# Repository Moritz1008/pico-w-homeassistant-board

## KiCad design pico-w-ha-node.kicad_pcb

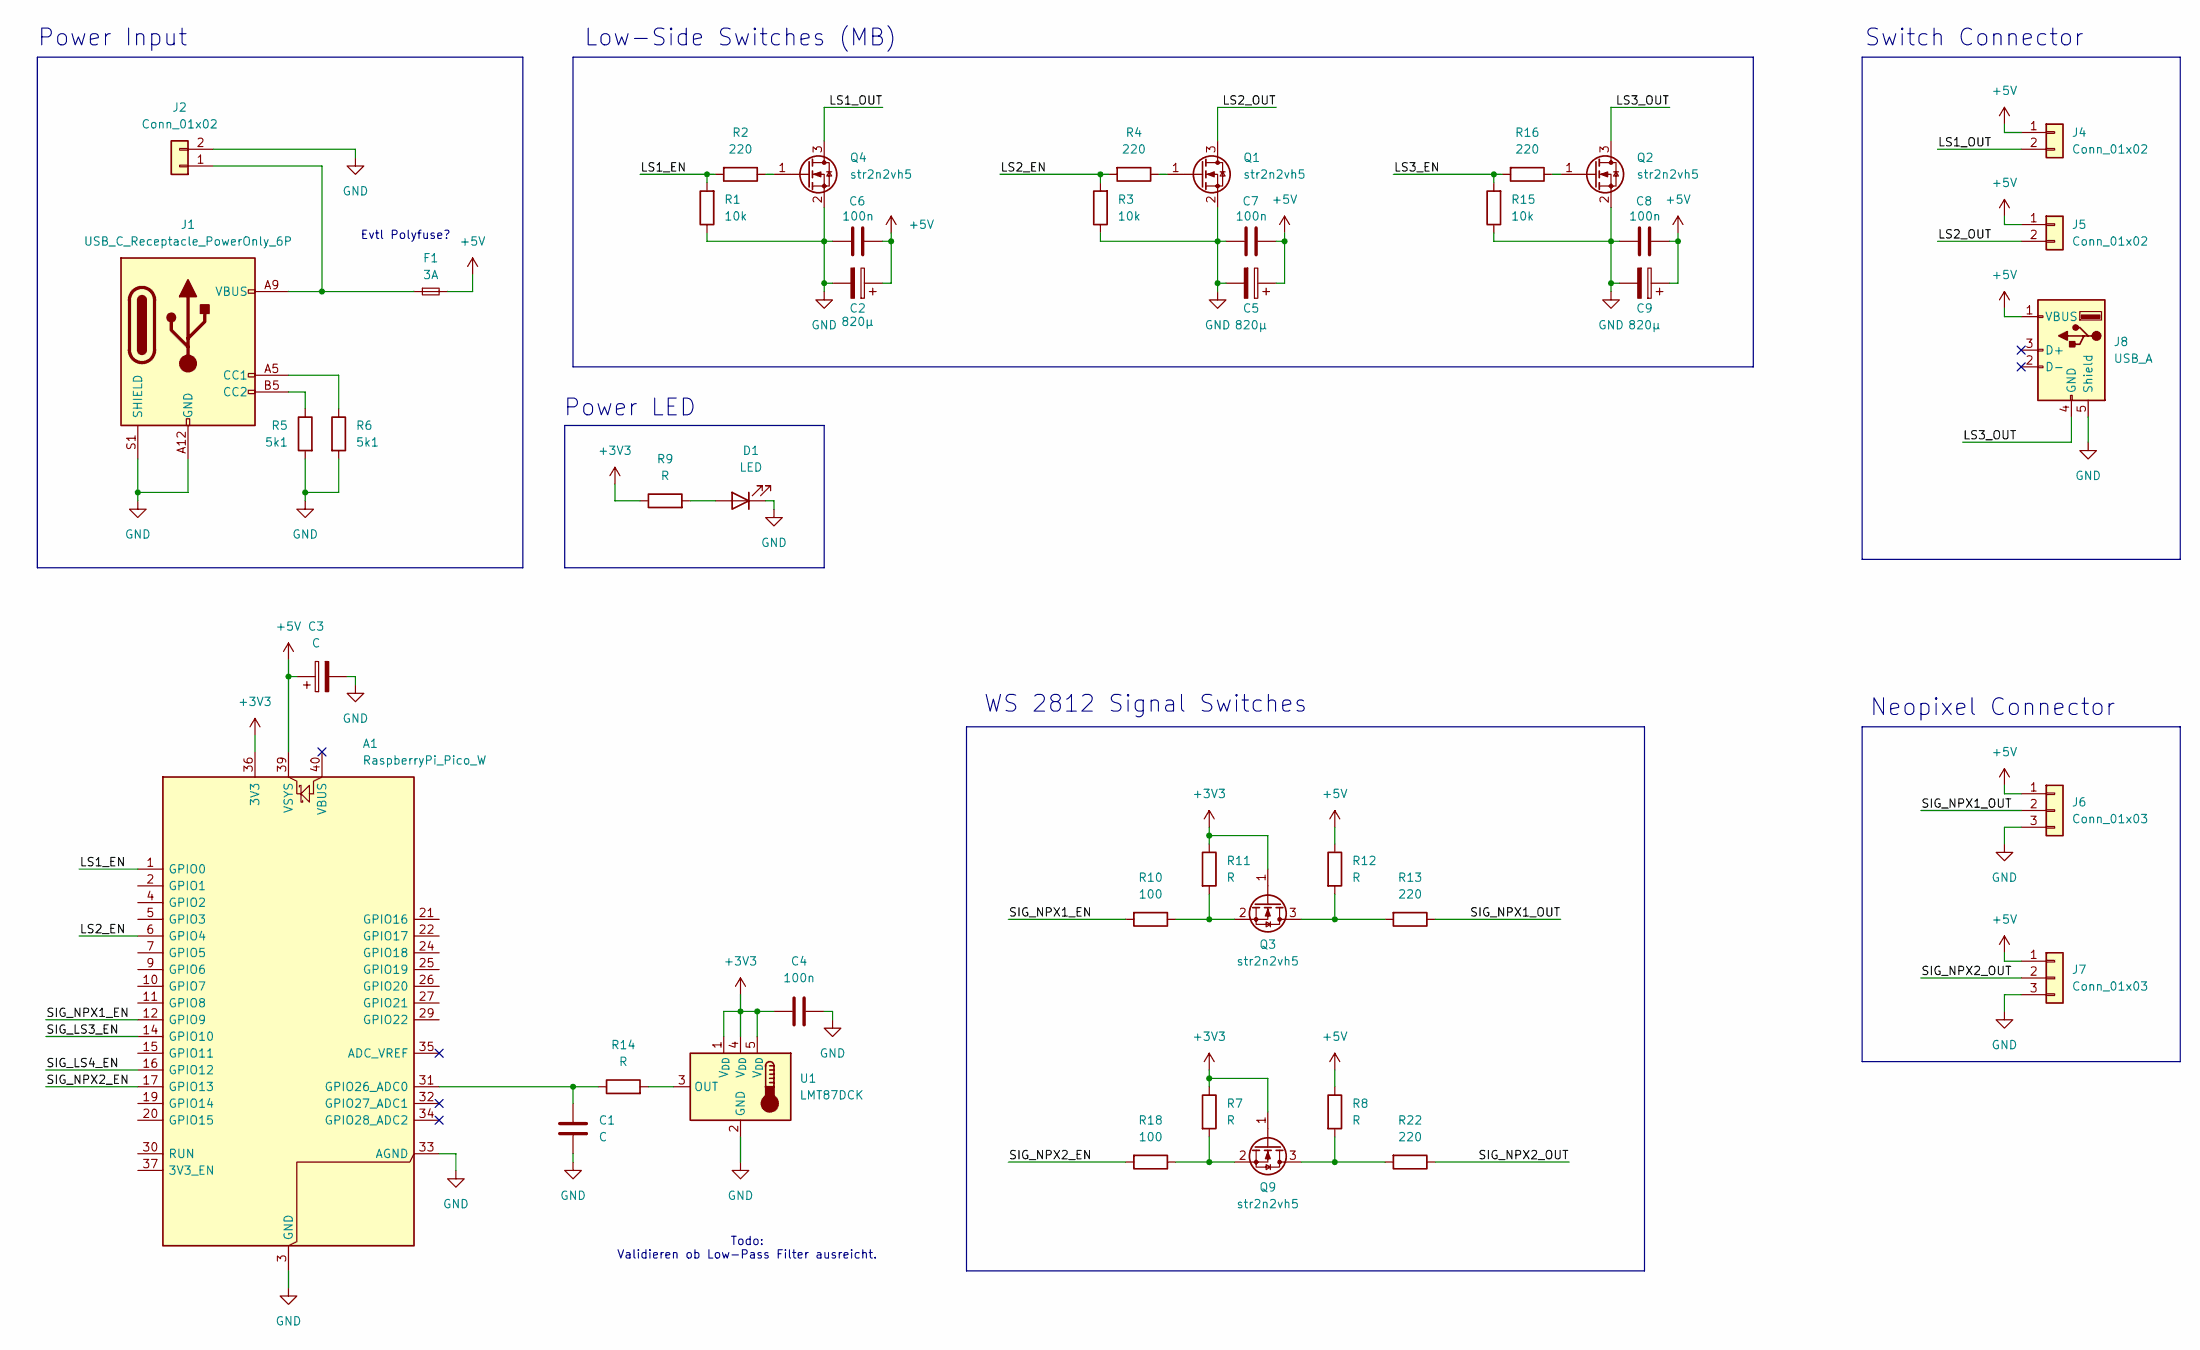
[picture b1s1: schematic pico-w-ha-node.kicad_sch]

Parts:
A1: RaspberryPi_Pico_W; RaspberryPi_Pico_W_SMD
C1: C; C_0603_1608Metric_Pad1.08x0.95mm_HandSolder
C2, C5, C9: 820µ; CP_Radial_D10.0mm_P5.00mm
C3: C; CP_Radial_D10.0mm_P5.00mm
C4: 100n; C_0603_1608Metric_Pad1.08x0.95mm_HandSolder
C6, C7, C8: 100n; C_0805_2012Metric
D1: LED; LED_0603_1608Metric_Pad1.05x0.95mm_HandSolder
F1: 3A; Fuse_1206_3216Metric
J1: USB_C_Receptacle_PowerOnly_6P; USB_C_Receptacle_GCT_USB4125-xx-x-0190_6P_TopMnt_Horizontal
J2: Conn_01x02; Molex_Micro-Fit_3.0_43650-0212_1x02-1MP_P3.00mm_Horizontal
J4, J5: Conn_01x02; Molex_CLIK-Mate_502585-0270_1x02-1MP_P1.50mm_Horizontal
J6, J7: Conn_01x03; Molex_CLIK-Mate_502585-0370_1x03-1MP_P1.50mm_Horizontal
J8: USB_A
Q1, Q2, Q3, Q4, Q9: str2n2vh5; SOT-23
R1, R3, R15: 10k; R_0603_1608Metric_Pad0.98x0.95mm_HandSolder
R2, R4, R13, R16, R22: 220; R_0603_1608Metric_Pad0.98x0.95mm_HandSolder
R5, R6: 5k1; R_0603_1608Metric_Pad0.98x0.95mm_HandSolder
R7, R8, R9, R11, R12, R14: R; R_0603_1608Metric_Pad0.98x0.95mm_HandSolder
R10, R18: 100; R_0603_1608Metric_Pad0.98x0.95mm_HandSolder
U1: LMT87DCK; SOT-353_SC-70-5

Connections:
+3V3: A1.36 (3V3), C4.1, Q3.1 (G), Q9.1 (G), R7.1, R9.1, R11.1, U1.1 (V_{DD}), U1.4 (V_{DD}), U1.5 (V_{DD})
+5V: A1.39 (VSYS), C2.1, C3.1, C5.1, C6.1, C7.1, C8.1, C9.1, F1.2, J4.1, J5.1, J6.1, J7.1, J8.1 (VBUS), R8.1, R12.1
/LS1_EN: A1.1 (GPIO0), R1.2, R2.2
/LS1_OUT: J4.2, Q4.3 (D)
/LS2_EN: A1.6 (GPIO4), R3.2, R4.2
/LS2_OUT: J5.2, Q1.3 (D)
/LS3_EN: R15.2, R16.2
/LS3_OUT: J8.4 (GND), Q2.3 (D)
/SIG_LS3_EN: A1.14 (GPIO10)
/SIG_LS4_EN: A1.16 (GPIO12)
/SIG_NPX1_EN: A1.12 (GPIO9), R10.2
/SIG_NPX1_OUT: J6.2, R13.1
/SIG_NPX2_EN: A1.17 (GPIO13), R18.2
/SIG_NPX2_OUT: J7.2, R22.1
GND: A1.3 (GND), A1.8 (GND), A1.13 (GND), A1.18 (GND), A1.23 (GND), A1.28 (GND), A1.33 (AGND), A1.38 (GND), C1.2, C2.2, C3.2, C4.2, C5.2, C6.2, C7.2, C8.2, C9.2, D1.1 (K), J1.A12 (GND), J1.B12 (GND), J1.S1 (SHIELD), J2.2, J6.3, J7.3, J8.5 (Shield), Q1.2 (S), Q2.2 (S), Q4.2 (S), R1.1, R3.1, R5.2, R6.2, R15.1, U1.2 (GND)
unnamed: A1.31 (GPIO26_ADC0), C1.1, R14.1
unnamed: D1.2 (A), R9.2
unnamed: J1.A5 (CC1), R6.1
unnamed: J1.B5 (CC2), R5.1
unnamed: F1.1, J1.A9 (VBUS), J1.B9 (VBUS), J2.1
unnamed: Q1.1 (G), R4.1
unnamed: Q2.1 (G), R16.1
unnamed: Q3.3 (D), R12.2, R13.2
unnamed: Q3.2 (S), R10.1, R11.2
unnamed: Q4.1 (G), R2.1
unnamed: Q9.3 (D), R8.2, R22.2
unnamed: Q9.2 (S), R7.2, R18.1
unnamed: R14.2, U1.3 (OUT)

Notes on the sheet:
Switch Connector
Low-Side Switches (MB)
Power LED
Neopixel Connector
Todo: Validieren ob Low-Pass Filter ausreicht.
WS 2812 Signal Switches
Evtl Polyfuse?
Power Input

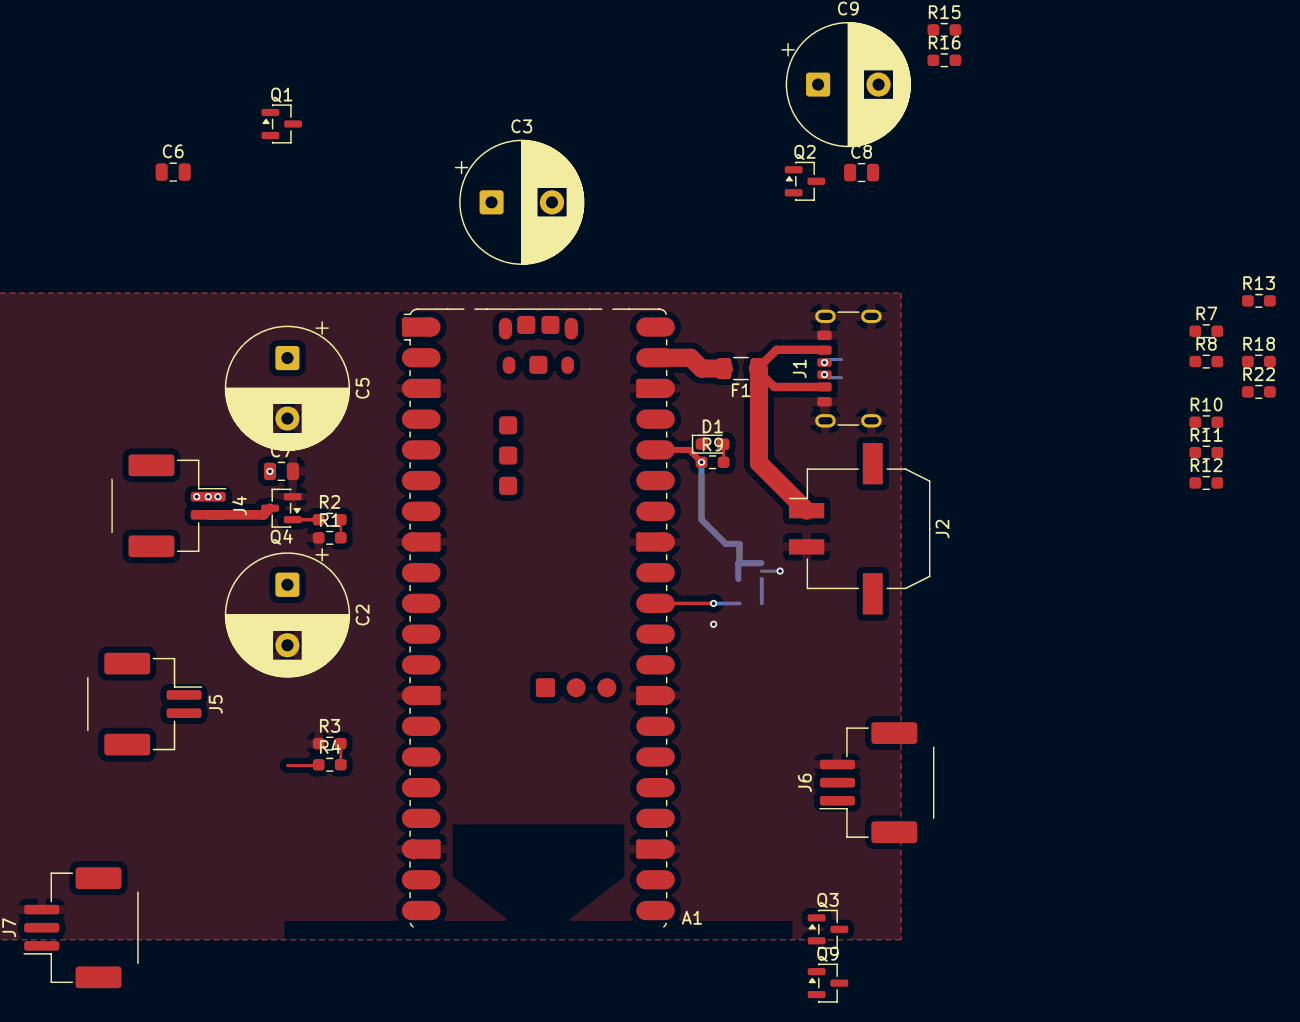
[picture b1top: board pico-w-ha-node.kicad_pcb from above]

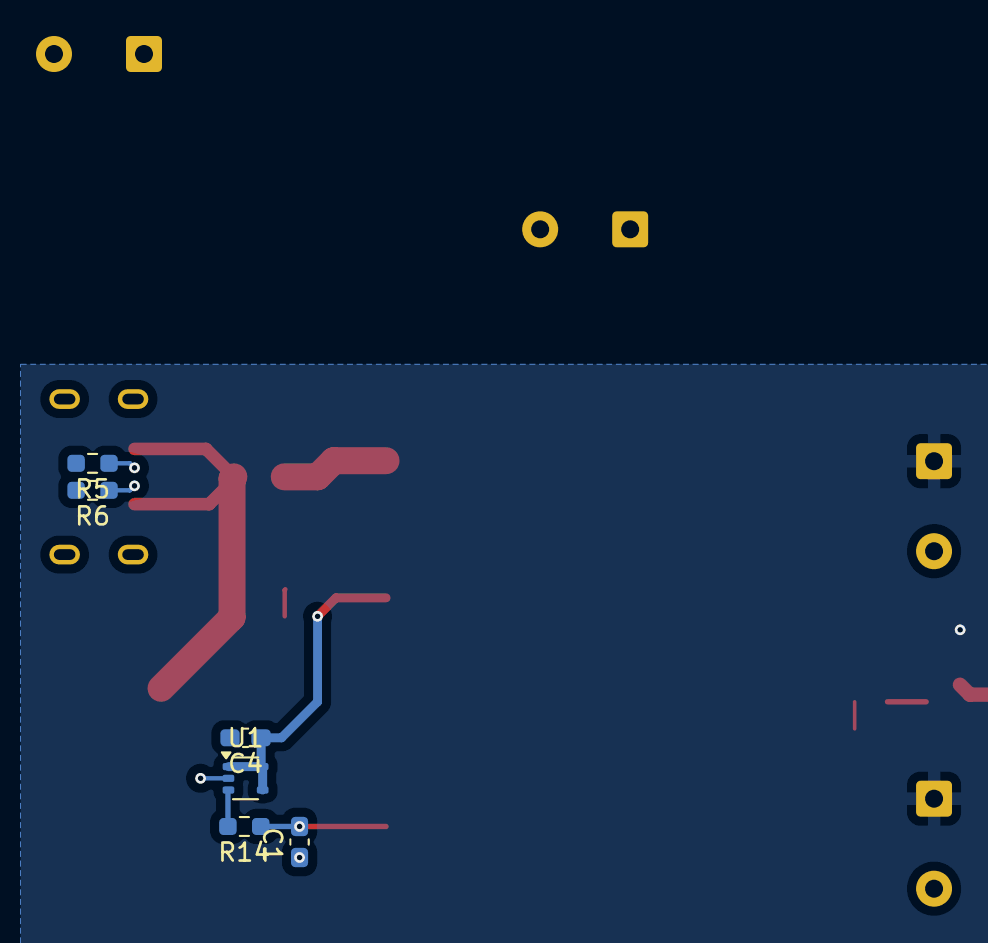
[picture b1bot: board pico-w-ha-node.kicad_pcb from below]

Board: 2 copper layers, 42 parts (6 on the bottom side), 25 nets.

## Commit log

2025-12-14 Changes NPX signal circuit, adds some capacitors, temperature sensor and alternative power input
2026-01-05 Adds 3rd output via USB-A and some additional capacitors.
